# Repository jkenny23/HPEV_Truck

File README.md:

# HPEV_Truck
1954 GMC Truck EV Conversion

due_can_shield_v11.sch/brd - This is a reverse engineered/cloned shield for the EVTV Can Due board that is part of the EVTV Tesla Model S Pack Controller found here: http://store.evtv.me/proddetail.php?prod=1FullpackController

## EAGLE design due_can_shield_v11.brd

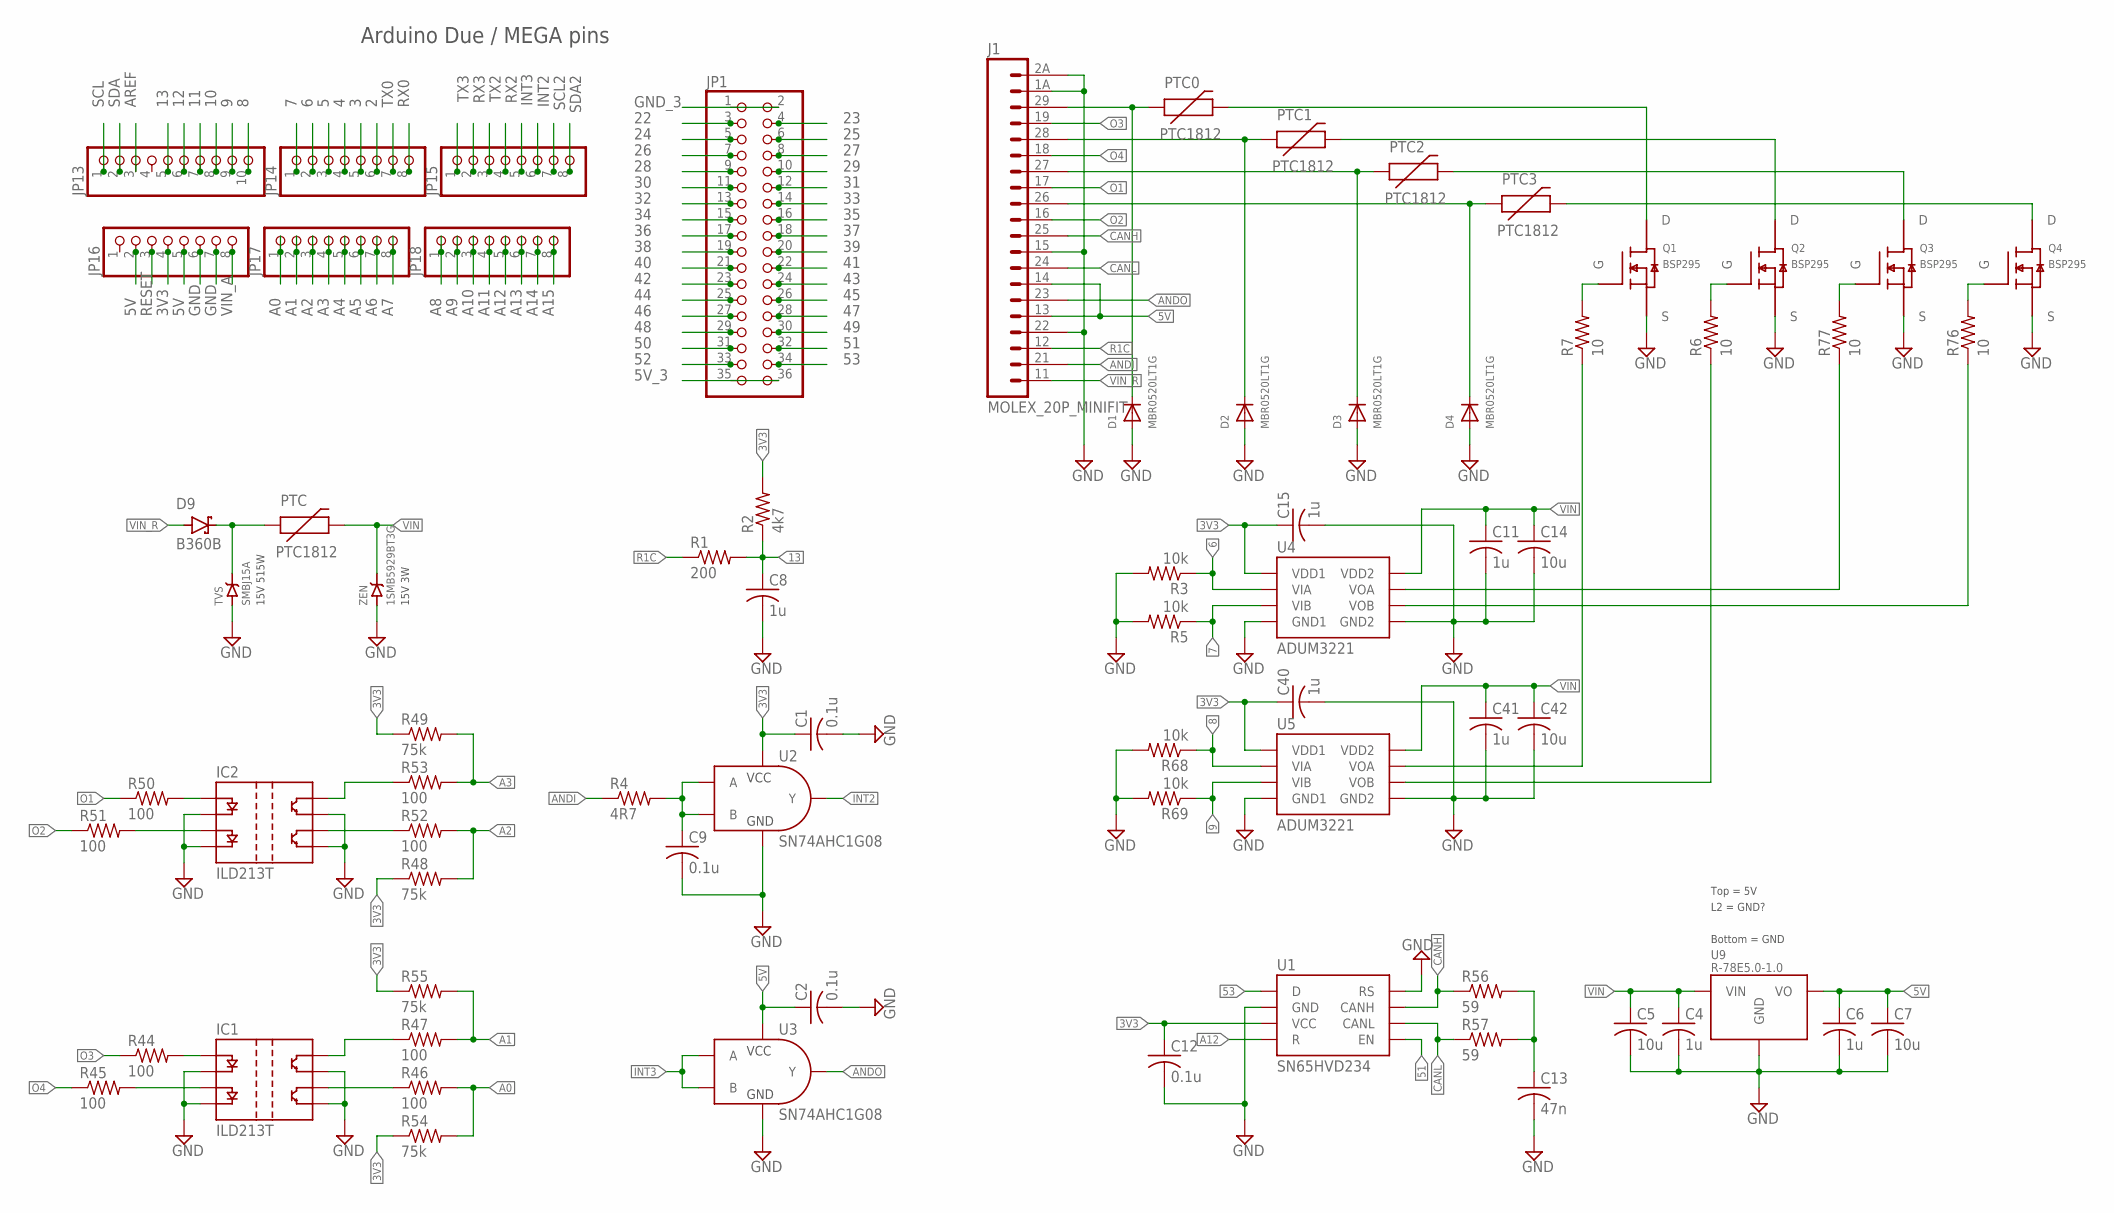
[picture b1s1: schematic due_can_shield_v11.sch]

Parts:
C1, C2, C9, C12: 0.1u; C0603
C4, C6, C8, C11, C15, C40, C41: 1u; C0805
C5, C7, C14, C42: 10u; C0805
C13: 47n; C0805
D1, D2, D3, D4: MBR0520LT1G; SOD-123
D9: B360B; DO-214AA_SMB
IC1, IC2: ILD213T; 8-SOIC
J1: MOLEX_20P_MINIFIT
JP1: PINHD-2X18; 2X18
JP13: PINHD-1X10; 1X10
JP14, JP15, JP16, JP17, JP18: PINHD-1X8; 1X08
PTC, PTC0, PTC1, PTC2, PTC3: PTC1812; 1812
Q1, Q2, Q3, Q4: BSP295; SOT223
R1: 200; R0603
R2: 4k7; R0603
R3, R5, R68, R69: 10k; R0402
R4: 4R7; R0603
R6, R7, R76, R77: 10; R0402
R44, R45, R46, R47, R50, R51, R52, R53: 100; R0402
R48, R49, R54, R55: 75k; R0402
R56, R57: 59; R0805
TVS: SMBJ15A; DO-214AA_SMB
U1: SN65HVD234; 8-SOIC
U2, U3: SN74AHC1G08; SC70-5
U4, U5: ADUM3221; 8-SOIC
U9: R-78E5.0-1.0
ZEN: 1SMB5929BT3G; DO-214AA_SMB

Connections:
2: JP14.6
3: JP14.5
3V3: C1.1, C12.1, C15.1, C40.1, JP16.4, R2.2, R48.1, R49.1, R54.1, R55.1, U1.3 (VCC), U2.5 (VCC), U4.1 (VDD1), U5.1 (VDD1)
4: JP14.4
5: JP14.3
5V: C2.1, C6.1, C7.1, J1.13, J1.14, JP16.2, JP16.5, U3.5 (VCC), U9.3-OUT (VO)
5V_3: JP1.36
6: JP14.2, R3.1, U4.2 (VIA)
7: JP14.1, R5.1, U4.3 (VIB)
8: JP13.10, R68.1, U5.2 (VIA)
9: JP13.9, R69.1, U5.3 (VIB)
10: JP13.8
11: JP13.7
12: JP13.6
13: C8.1, JP13.5, R1.2, R2.1
22: JP1.3
23: JP1.4
24: JP1.5
25: JP1.6
26: JP1.7
27: JP1.8
28: JP1.9
29: JP1.10
30: JP1.11
31: JP1.12
32: JP1.13
33: JP1.14
34: JP1.15
35: JP1.16
36: JP1.17
37: JP1.18
38: JP1.19
39: JP1.20
40: JP1.21
41: JP1.22
42: JP1.23
43: JP1.24
44: JP1.25
45: JP1.26
46: JP1.27
47: JP1.28
48: JP1.29
49: JP1.30
50: JP1.31
51: JP1.32, U1.5 (EN)
52: JP1.33
53: JP1.34, U1.1 (D)
A0: JP17.1, R46.2, R54.2
A1: JP17.2, R47.2, R55.2
A2: JP17.3, R48.2, R52.2
A3: JP17.4, R49.2, R53.2
A4: JP17.5
A5: JP17.6
A6: JP17.7
A7: JP17.8
A8: JP18.1
A9: JP18.2
A10: JP18.3
A11: JP18.4
A12: JP18.5, U1.4 (R)
A13: JP18.6
A14: JP18.7
A15: JP18.8
ANDI: J1.21, R4.1
ANDO: J1.23, U3.4 (Y)
AREF: JP13.3
CANH: J1.25, R56.1, U1.7 (CANH)
CANL: J1.24, R57.1, U1.6 (CANL)
GND: C1.2, C2.2, C4.2, C5.2, C6.2, C7.2, C8.2, C9.2, C11.2, C12.2, C13.2, C14.2, C15.2, C40.2, C41.2, C42.2, D1.A, D2.A, D3.A, D4.A, IC1.2 (K1), IC1.4 (K2), IC1.5 (E2), IC1.7 (E1), IC2.2 (K1), IC2.4 (K2), IC2.5 (E2), IC2.7 (E1), J1.1A, J1.2A, J1.15, J1.22, JP16.6, JP16.7, Q1.3 (S), Q2.3 (S), Q3.3 (S), Q4.3 (S), R3.2, R5.2, R68.2, R69.2, TVS.A, U1.2 (GND), U1.8 (RS), U2.3 (GND), U3.3 (GND), U4.4 (GND1), U4.5 (GND2), U5.4 (GND1), U5.5 (GND2), U9.2-GND (GND), ZEN.A
GND_3: JP1.2
INT2: JP15.6, U2.4 (Y)
INT3: JP15.5, U3.1 (A), U3.2 (B)
unnamed: D1.C, J1.29, PTC0.1
unnamed: D2.C, J1.28, PTC1.1
unnamed: D3.C, J1.27, PTC2.1
unnamed: D4.C, J1.26, PTC3.1
unnamed: R77.1, U4.7 (VOA)
unnamed: R76.1, U4.6 (VOB)
unnamed: PTC0.2, Q1.2 (D), Q1.4 (D)
unnamed: PTC1.2, Q2.2 (D), Q2.4 (D)
unnamed: PTC2.2, Q3.2 (D), Q3.4 (D)
unnamed: IC2.1 (A1), R50.2
unnamed: PTC3.2, Q4.2 (D), Q4.4 (D)
unnamed: D9.K (CATHODE), PTC.1, TVS.K
unnamed: Q1.1 (G), R7.2
unnamed: Q2.1 (G), R6.2
unnamed: Q3.1 (G), R77.2
unnamed: Q4.1 (G), R76.2
unnamed: R7.1, U5.7 (VOA)
unnamed: R6.1, U5.6 (VOB)
unnamed: IC2.3 (A2), R51.2
unnamed: C13.1, R56.2, R57.2
unnamed: IC1.1 (A1), R44.2
unnamed: IC1.3 (A2), R45.2
unnamed: IC2.8 (C1), R53.1
unnamed: IC2.6 (C2), R52.1
unnamed: IC1.8 (C1), R47.1
unnamed: IC1.6 (C2), R46.1
unnamed: C9.1, R4.2, U2.1 (A), U2.2 (B)
O1: J1.17, R50.1
O2: J1.16, R51.1
O3: J1.19, R44.1
O4: J1.18, R45.1
R1C: J1.12, R1.1
RESET: JP16.3
RX0: JP14.8
RX2: JP15.4
RX3: JP15.2
SCL: JP13.1
SCL2: JP15.7
SDA: JP13.2
SDA2: JP15.8
TX0: JP14.7
TX2: JP15.3
TX3: JP15.1
VIN: C4.1, C5.1, C11.1, C14.1, C41.1, C42.1, PTC.2, U4.8 (VDD2), U5.8 (VDD2), U9.1-IN (VIN), ZEN.K
VIN_A: JP16.8
VIN_R: D9.A (ANODE), J1.11

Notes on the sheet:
Arduino Due / MEGA pins
Top = 5V
15V 3W
15V 515W
Bottom = GND
L2 = GND?

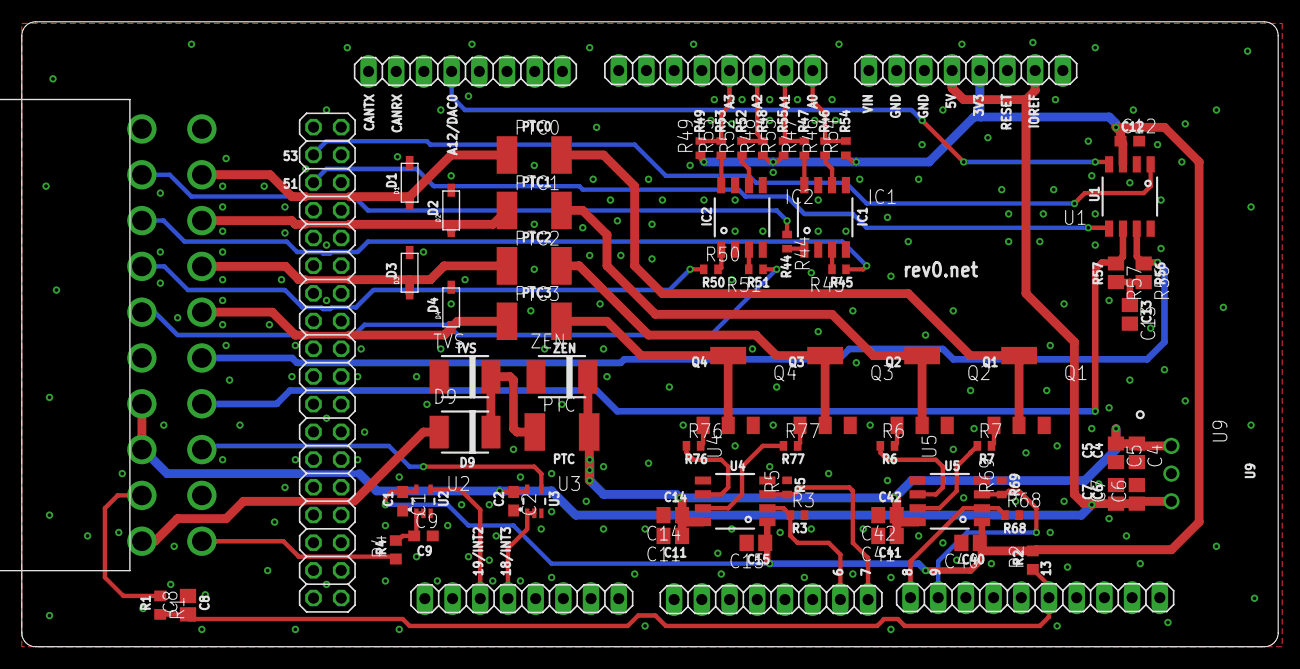
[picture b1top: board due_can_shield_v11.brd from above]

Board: 2 copper layers, 115.2 x 57.3 mm, 73 parts (0 on the bottom side), 55 nets.

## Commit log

2020-11-17 Create temp
